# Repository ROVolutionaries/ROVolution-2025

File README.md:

# ROVolution 2025 Open-Sourced Resources

## **Table of Contents**

* [Hardware](./Hardware) — PCB designs for the ROV’s Power Distribution and Control Boards, created in KiCad with accompanying schematics, layouts, and 3D models.
* [Software](./Software) — Python and C++ code for ROV control, communication, and image processing, including surface interfaces, Raspberry Pi and Pico firmware, and testing utilities.
* [Model](./Model) — 3D models, renders, and Fusion 360 assemblies of the ROV components
* [Ocean Exploration Video Challenge](./Ocean%20Exploration%20Video%20Challenge) — Object detection and classification of ocean species for the NOAA Ocean Exploration Video Challenge. 

---

## **Contributions and Disclaimers**

This repository represents a portion of the overall ROVolution 2025 project, focusing primarily on **design, software development, and task-specific coding**. It does **not include full ROVolutionaries work**. This repository only highlights the contributions specifically carried out by the following members:

* **Konstantin Logashenko (CEO)** — PCB design and software.
* **Dewei David Zhang (CTO)** — CAD design and code contributions.
* **Muhammad Ahmed Shaikh (former CEO)** — software and code contributions.

---

## **More on ROVolution**

* [YouTube](https://www.youtube.com/@ROVolutionaries)
* [Instagram](https://www.instagram.com/rovolutionaries/)
* [Technical Documentation](https://drive.google.com/file/d/1zGqDDCye5YSRfjU_IAGbzJyzfevygd78/view?usp=sharing)
* [Additional Files](https://docs.google.com/spreadsheets/d/10eZ-Em9sXnn5XWBDeCyZJDLGmav5vlog2l0rmnmTBGw/edit?gid=2110360715#gid=2110360715)

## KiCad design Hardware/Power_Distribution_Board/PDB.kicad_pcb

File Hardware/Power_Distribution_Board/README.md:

Project created in KiCAD 8.0
PCB for distributing 12V and 5V power to other component
12 V XT60 Connectors for 8 ESCs, 2 for auxillary components
5V JST8 Connector
Parallel capacitance added on 12 V tether line to balance out tether inductance, reducing voltage spikes due to changes in current drad
TVS diode to protect if transient voltage spikes do occur as described above

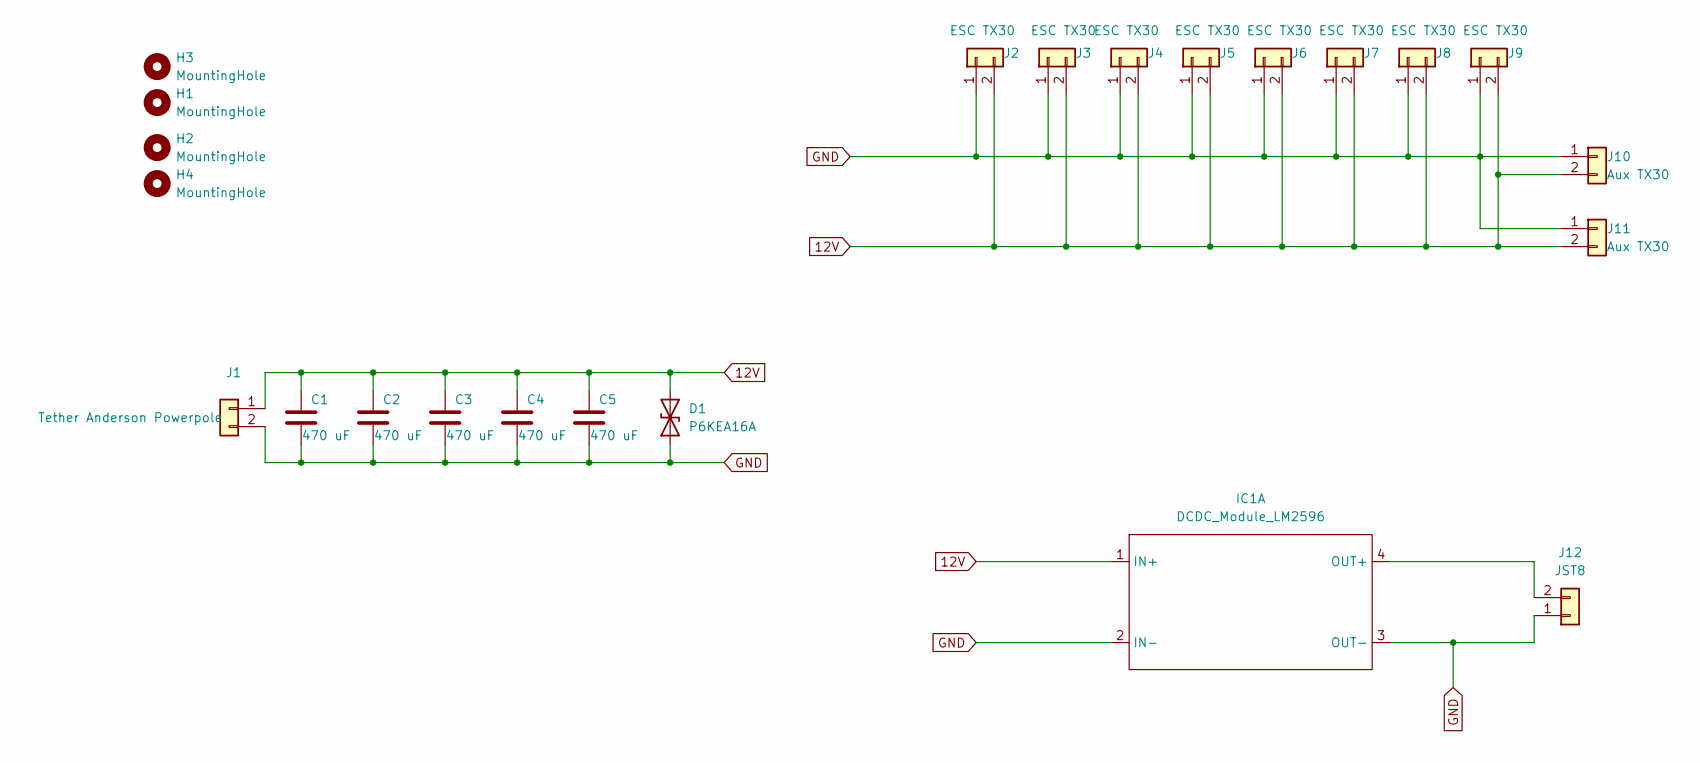
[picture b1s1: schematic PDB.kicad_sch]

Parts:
C1, C2, C3, C4, C5: 470 uF; CP_Radial_D10.0mm_P3.50mm
D1: P6KEA16A; D_DO-15_P12.70mm_Horizontal
H1, H2, H3, H4: MountingHole; MountingHole_4.3mm_M4
IC1: DCDC_Module_LM2596; DCDC_Module_2596
J1: Tether Anderson Powerpole; TerminalBlock_bornier-2_P5.08mm
J2, J3, J4, J5, J6, J7, J8, J9: ESC TX30; AMASS_XT30U-M_1x02_P5.0mm_Vertical
J10, J11: Aux TX30; AMASS_XT30U-M_1x02_P5.0mm_Vertical
J12: JST8; JST_XH_S2B-XH-A_1x02_P2.50mm_Horizontal

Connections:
12V: C1.1, C2.1, C3.1, C4.1, C5.1, D1.2 (A2), IC1.1 (IN+), J1.1, J2.2, J3.2, J4.2, J5.2, J6.2, J7.2, J8.2, J9.2, J10.2, J11.2
GND: C1.2, C2.2, C3.2, C4.2, C5.2, D1.1 (A1), IC1.2 (IN-), IC1.3 (OUT-), J1.2, J2.1, J3.1, J4.1, J5.1, J6.1, J7.1, J8.1, J9.1, J10.1, J11.1, J12.1
unnamed: IC1.4 (OUT+), J12.2

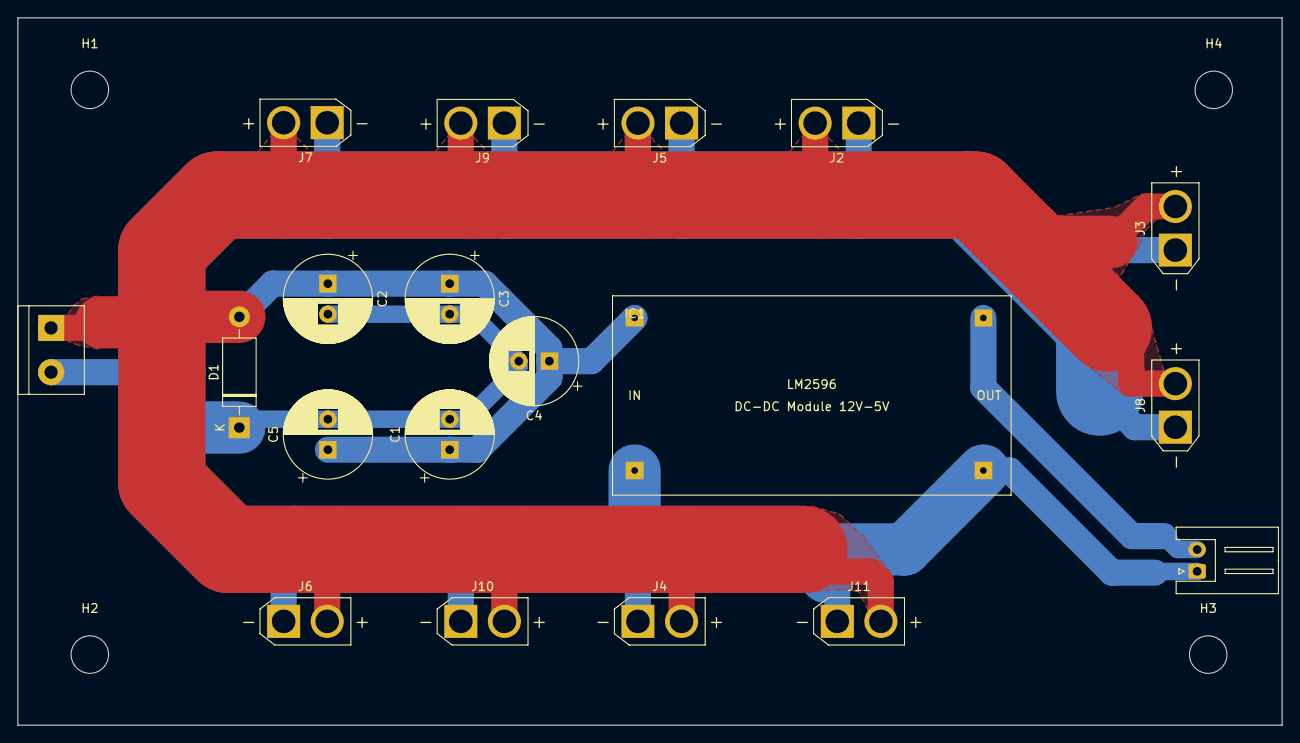
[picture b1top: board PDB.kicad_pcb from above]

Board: 2 copper layers, 145.0 x 81.1 mm, 23 parts (0 on the bottom side), 3 nets.

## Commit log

2024-12-21 Moved files from personal repo to official ROVolution-2025
2024-12-21 Added logic loop to pico script.
2024-12-21 Resolved errors
2024-12-21 Added ps5 controller testing script
2024-12-21 added test-code
2024-12-22 Added dead zone to joystick tester.
2024-12-22 Tested with Iyads controller to find correct button values
2024-12-23 Added 8 directions of motion to joystick
2024-12-23 Corrected angle boundaries after testing with Iyad
2024-12-23 Made the joystick code more compact
2024-12-30 Added basic PID logic for stabilisation
2024-12-30 Organised
2025-01-13 Added IMU script
2025-02-06 Changed pico to master
2025-02-25 Added C++ file for pico to enable slave mode
2025-02-26 Used pico SDK slave API to properly implement slave functionality
2025-02-26 Updated C++ file
2025-02-26 successful compilation
2025-03-08 plotted coordinates of river
2025-03-08 completed invasive carp
    😜 👍
2025-03-08 renamed?
2025-03-08 improved aesthetics
2025-04-14 Updated ROV code
2025-05-06 Updated pico code and added UDP functionality
2025-10-23 word to md test
2025-10-24 upload files
2025-10-24 tech doc upload
2025-10-24 update object detection file
2025-10-24 documentation
2025-10-24 step file upload
2025-10-24 created hardware section
2025-10-24 upload pcb
2025-10-25 thrust test
2025-10-25 Update README.md in Model
2025-10-30 Directory for Power Board
2025-10-30 Upload KiCAD files for Power Board
2025-10-30 Create directory for Logic PCB
2025-10-30 Upload KiCAD files for control board
2025-11-02 update hardware readme file
2025-11-02 small update to readme
2025-11-09 mit license
